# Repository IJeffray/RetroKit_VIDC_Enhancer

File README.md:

# Retro Kit "Ultimate" VIDC Enhancer

This project is a direct Altium import of Paul Vernon's Eagle files for his VIDC Enhancer.  All credit to Paul.  The following is his original documentation:

## VIDC Enhancer v2.03 (Ultra VIDC Enhancer)

The Ultra VIDC Enhancer provides a way to deliver the choice of up to four different clock signals including the on board 24MHz clock the the VIDC1a chip fitted to early Archimedes which could only provide a 24MHz clock signal by themselves.

Typically, a 25.175MHz and 36MHz oscillator are fitted to the board with a 220R pull down resistor in place of a possible third oscillator which, if fitted would allow you to overclock the VIDC chip beyond 36MHz.

Control and selection of the four clock signals is done by way of using the Aux IO connector on the Archimedes motherboard. Where previous VIDC Enhancers used just one connection to enable and disable the VIDC Enhancer clock provided, the Ultra VIDC Enhancer uses both connections as a binary pair to deliver the selection of VIDCCLK 0 through to VIDCCLK3 which are 24MHz, 25.175MHz, 36MHz and a custom speed respectively.

The clock selection is achieved by passing the clock signals through a non-inverting multiplexer which allows each of the four inputs to be individually selected for output.

## Sync on Green fix

The Sync on Green fix as found on version 1 of the VIDC Enhancer has been incorporated into the Ultra VIDC Enhancer to deliver the same level of functionality to older Archimedes machines that is provided by the A540 and later Acorn machines such as the A30x0, A4000 and A5000 machines and allows (S)VGA monitors to be connected to the Archimedes without losing the green component of the video signal.

## Overclocking

Overclocking the VIDC chip could lead to permanent damage of the VIDC chip or other associated hardware in your Archimedes. If you choose to fit an oscillator to overclock your VIDC chip beyond 36MHz, you do so at your own risk.

## VIDC Enhancer Vs. Ultra VIDC Enhancer

There are several differences between the VIDC Enhancer and the Ultra VIDC Enhancer which are outlined here:

* PCB design features a double sided full pour ground plane to reduce signal noise.
* Fewer logic gates are used to switch the clock signals
* Design provides improved power smoothing facilities
* Current protection resistors are present to protect the multiplexer IC and VIDC1a chip
* Only supports half-can oscillators
* Only marginally larger than the original design but delivers far more functionality
* No support for manual hardware control
* Only needs a single PCB to deliver multiple VIDC clock frequencies therefore has a much lower profile when fitted.

## Credits

The design of the Ultra VIDC Enhancer is my own design however I owe a debt of gratitude to Mr. Martin Barr who provided sanity checks for my design and put up with my endless photo's and video's of sinusoidal waves of different frequencies and quality as I developed the design on a breadboard.

The software to control the Ultra VIDC Enhancer is based on Andreas Barth's <a href="http://www.barth-welt.de/alt/1998/acorn/indexuk.htm">AutoVIDC module</a> for which he gave me permission to modify and distribute the updated version.</a>
<p>I'd also like to thank Jon Abbott and Steve Harrison who both provided suggestions and encouragement in developing extra features into the RISC OS module, AutoVIDC.

## Further information

For further information, you can visit the Retro-Kit [Ultra VIDC Enhancer page](http://www.retro-kit.co.uk/Ultra-VIDC-Enhancer/)

[http://www.retro-kit.co.uk](http://www.retro-kit.co.uk)

[Notes.txt](Notes.txt)

[VIDC-Enhancer-manual-v2.pdf](VIDC-Enhancer-manual-v2.pdf)

[VIDC-Enhancer-AutoVIDC.pdf](VIDC-Enhancer-AutoVIDC.pdf)

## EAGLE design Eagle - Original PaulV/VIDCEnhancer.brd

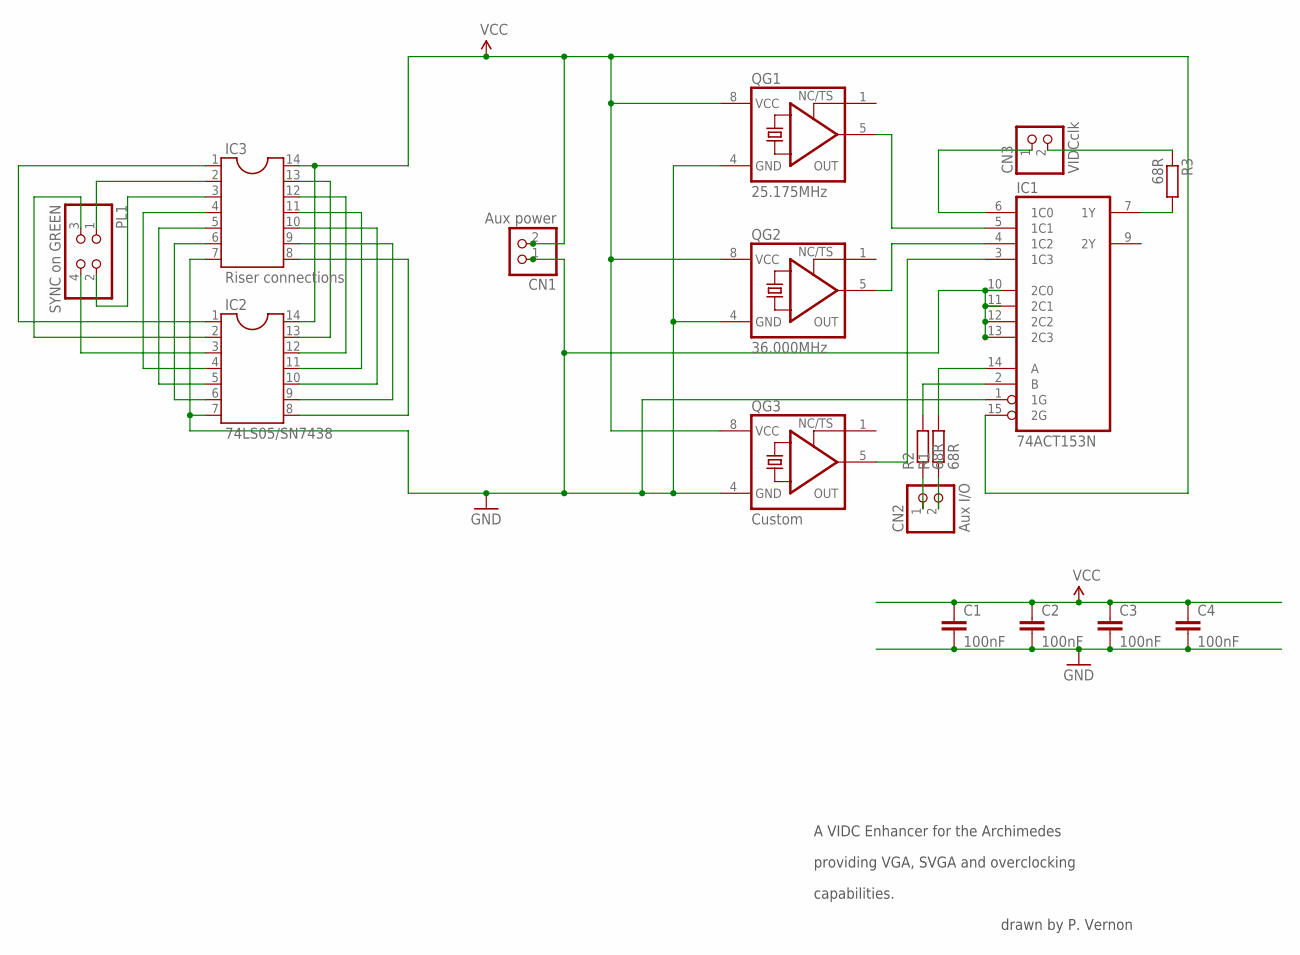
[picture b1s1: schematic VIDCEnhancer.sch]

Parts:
C1, C2, C3, C4: 100nF; C025-025X050
CN1: Aux power; 1X02/90
CN2: Aux I/O; 1X02/90
CN3: VIDCclk; 1X02/90
IC1: 74ACT153N; DIL16
IC2: 74LS05/SN7438; SOCKET-14
IC3: Riser connections; SOCKET-14
PL1: SYNC on GREEN; 2X02
QG1: 25.175MHz; DIL08S
QG2: 36.000MHz; DIL08S
QG3: Custom; DIL08S
R1, R2, R3: 68R; 0207/10

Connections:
GND: C1.2, C2.2, C3.2, C4.2, CN1.1, IC1.1 (1G), IC1.8 (GND), IC1.10 (2C0), IC1.11 (2C1), IC1.12 (2C2), IC1.13 (2C3), IC2.7, IC3.7, QG1.4 (GND), QG2.4 (GND), QG3.4 (GND)
unnamed: IC1.5 (1C1), QG1.5 (OUT)
unnamed: IC1.4 (1C2), QG2.5 (OUT)
unnamed: IC1.3 (1C3), QG3.5 (OUT)
unnamed: IC1.7 (1Y), R3.2
unnamed: CN3.1, IC1.6 (1C0)
unnamed: CN2.2, R1.1
unnamed: CN2.1, R2.1
unnamed: IC2.3, PL1.4
unnamed: IC1.2 (B), R2.2
unnamed: IC1.14 (A), R1.2
unnamed: CN3.2, R3.1
unnamed: IC2.6, IC3.6
unnamed: IC2.5, IC3.5
unnamed: IC2.4, IC3.4
unnamed: IC3.3, PL1.2
unnamed: IC3.2, PL1.1
unnamed: IC2.1, IC3.1
unnamed: IC2.13, IC3.13
unnamed: IC2.12, IC3.12
unnamed: IC2.11, IC3.11
unnamed: IC2.10, IC3.10
unnamed: IC2.9, IC3.9
unnamed: IC2.8, IC3.8
unnamed: IC2.2, PL1.3
VCC: C1.1, C2.1, C3.1, C4.1, CN1.2, IC1.15 (2G), IC1.16 (VCC), IC2.14, IC3.14, QG1.8 (VCC), QG2.8 (VCC), QG3.8 (VCC)

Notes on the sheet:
drawn by P. Vernon
providing VGA, SVGA and overclocking
A VIDC Enhancer for the Archimedes
capabilities.

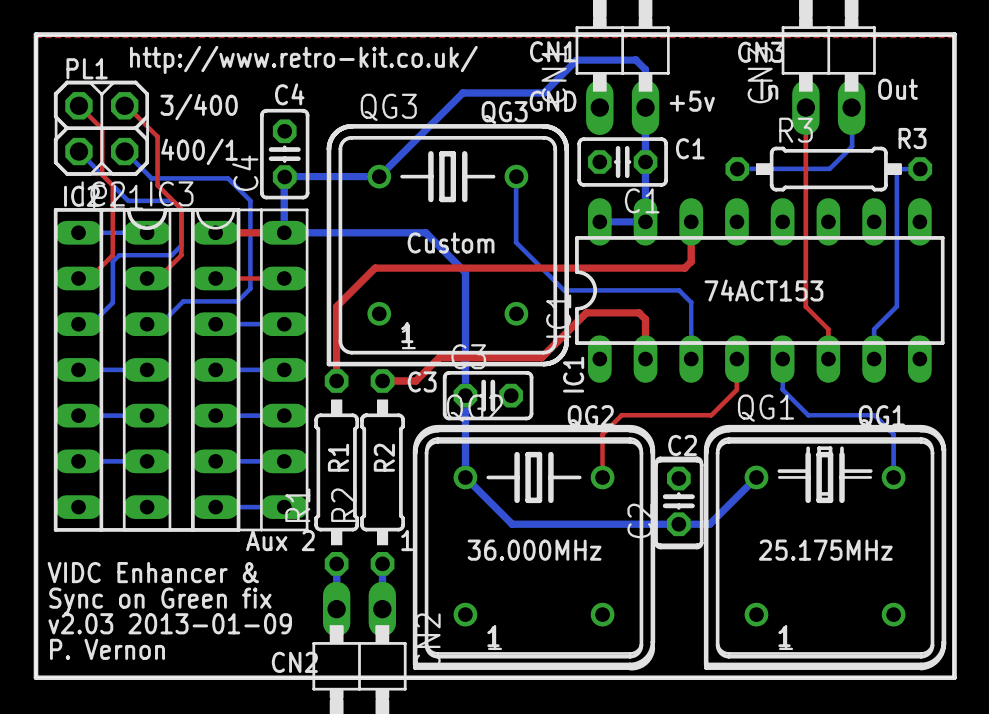
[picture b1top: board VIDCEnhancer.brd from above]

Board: 2 copper layers, 51.0 x 35.7 mm, 17 parts (0 on the bottom side), 26 nets.

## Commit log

2026-01-31 Initial commit from 2021
2026-01-31 Tweak README links for GitHub

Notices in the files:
parts and their libraries:
SparkFun: Licensing: CC v3.0 Share-Alike You are welcome to use this library for commercial purposes.
